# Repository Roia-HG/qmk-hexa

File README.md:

# qmk-hexa

 RP2040 칩을 사용한 멀티배열 스플릿 키보드

 3d 모델은 마그네틱 포고핀과 결합하는 구멍간격을 잘못 측정해서(데이터가 없었던 걸로 기억함) 개선이 필요함
그대로 사용하면 나처럼 한쪽을 약간 잘라서 사용해야하는 불상사가 일어남

 메인 오른쪽은 왼쪽 마그네틱 포고핀과 선을 연결하지 않음
양쪽 메인이 접속되면 row열 신호에 혼란이 발생하여 오류가 생길 것이기 때문에 스위치를 설치하는 것도 생각했지만
스위치를 설치할 적절한 방법이 떠오르지 않고 귀찮았으므로 연결하지 않고 사용하는 것으로 진행
즉, 메인 왼쪽은 네비키와 넘패드키 모두 좌우로 장착 가능하지만 메인 오른쪽은 오른쪽에만 장착 가능함.

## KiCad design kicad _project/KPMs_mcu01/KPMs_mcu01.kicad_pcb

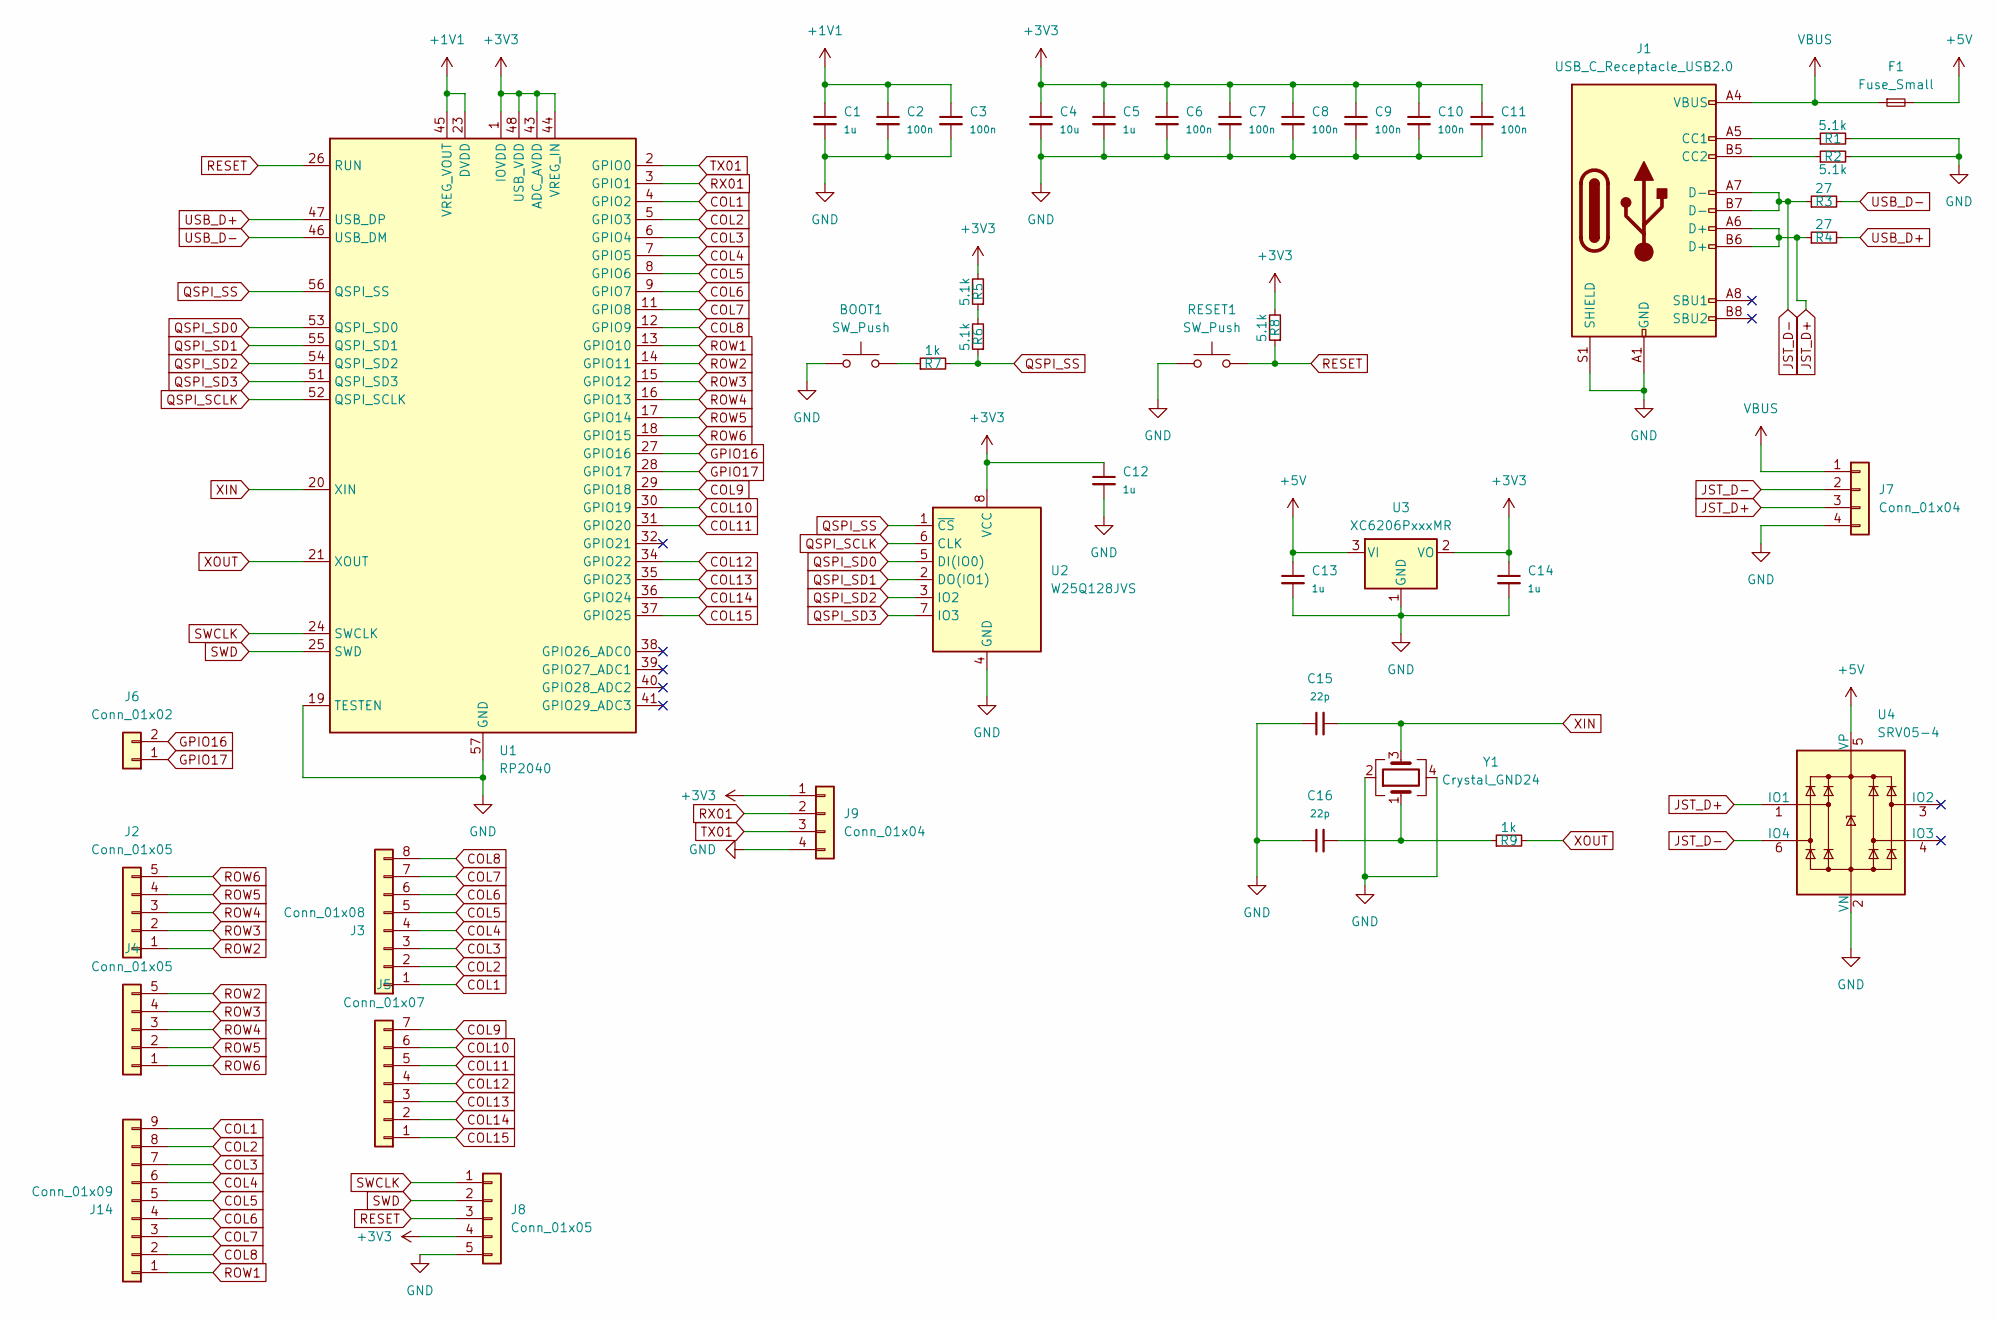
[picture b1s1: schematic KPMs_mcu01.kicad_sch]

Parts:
BOOT1: SW_Push; SW_SPST_TL3342
C1, C5, C12, C13, C14: 1u; C_0402_1005Metric
C2, C3, C6, C7, C8, C9, C10, C11: 100n; C_0402_1005Metric
C4: 10u; C_0402_1005Metric
C15, C16: 22p; C_0402_1005Metric
F1: Fuse_Small; MF-MSMF050-2
J1: USB_C_Receptacle_USB2.0; USB_C_Receptacle_HRO_TYPE-C-31-M-12
J2, J4: Conn_01x05; JST_SH_SM05B-SRSS-TB_1x05-1MP_P1.00mm_Horizontal
J3: Conn_01x08; JST_SH_SM08B-SRSS-TB_1x08-1MP_P1.00mm_Horizontal
J5: Conn_01x07; JST_SH_SM07B-SRSS-TB_1x07-1MP_P1.00mm_Horizontal
J6: Conn_01x02; PinHeader_1x02_P2.54mm_Vertical
J7, J9: Conn_01x04; JST_SH_SM04B-SRSS-TB_1x04-1MP_P1.00mm_Horizontal
J8: Conn_01x05; PinHeader_1x05_P2.00mm_Vertical
J14: Conn_01x09; JST_SH_SM09B-SRSS-TB_1x09-1MP_P1.00mm_Horizontal
R1, R2, R5, R6, R8: 5.1k; R_0402_1005Metric
R3, R4: 27; R_0402_1005Metric
R7, R9: 1k; R_0402_1005Metric
RESET1: SW_Push; SW_SPST_TL3342
U1: RP2040; QFN-56-1EP_7x7mm_P0.4mm_EP3.2x3.2mm
U2: W25Q128JVS; SOIC-8_5.23x5.23mm_P1.27mm
U3: XC6206PxxxMR; SOT-23-3
U4: SRV05-4; SOT-23-6-routable
Y1: Crystal_GND24; Crystal_SMD_3225-4Pin_3.2x2.5mm

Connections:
+1V1: C1.1, C2.1, C3.1, U1.23 (DVDD), U1.45 (VREG_VOUT), U1.50 (DVDD)
+3V3: C4.1, C5.1, C6.1, C7.1, C8.1, C9.1, C10.1, C11.1, C12.1, C14.1, J8.4, J9.1, R5.2, R8.2, U1.1 (IOVDD), U1.10 (IOVDD), U1.22 (IOVDD), U1.33 (IOVDD), U1.42 (IOVDD), U1.43 (ADC_AVDD), U1.44 (VREG_IN), U1.48 (USB_VDD), U1.49 (IOVDD), U2.8 (VCC), U3.2 (VO)
+5V: C13.1, F1.2, U3.3 (VI), U4.5 (VP)
COL1: J3.1, J14.9, U1.4 (GPIO2)
COL2: J3.2, J14.8, U1.5 (GPIO3)
COL3: J3.3, J14.7, U1.6 (GPIO4)
COL4: J3.4, J14.6, U1.7 (GPIO5)
COL5: J3.5, J14.5, U1.8 (GPIO6)
COL6: J3.6, J14.4, U1.9 (GPIO7)
COL7: J3.7, J14.3, U1.11 (GPIO8)
COL8: J3.8, J14.2, U1.12 (GPIO9)
COL9: J5.7, U1.29 (GPIO18)
COL10: J5.6, U1.30 (GPIO19)
COL11: J5.5, U1.31 (GPIO20)
COL12: J5.4, U1.34 (GPIO22)
COL13: J5.3, U1.35 (GPIO23)
COL14: J5.2, U1.36 (GPIO24)
COL15: J5.1, U1.37 (GPIO25)
GND: BOOT1.1, C1.2, C2.2, C3.2, C4.2, C5.2, C6.2, C7.2, C8.2, C9.2, C10.2, C11.2, C12.2, C13.2, C14.2, C15.1, C16.1, J1.A1 (GND), J1.A12 (GND), J1.B1 (GND), J1.B12 (GND), J1.S1 (SHIELD), J7.4, J8.5, J9.4, R1.2, R2.2, RESET1.1, U1.19 (TESTEN), U1.57 (GND), U2.4 (GND), U3.1 (GND), U4.2 (VN), Y1.2, Y1.4
GPIO16: J6.2, U1.27 (GPIO16)
GPIO17: J6.1, U1.28 (GPIO17)
JST_D+: J1.A6 (D+), J1.B6 (D+), J7.3, R4.1, U4.1 (IO1)
JST_D-: J1.A7 (D-), J1.B7 (D-), J7.2, R3.1, U4.6 (IO4)
unnamed: BOOT1.2, R7.1
unnamed: C16.2, R9.1, Y1.1
unnamed: J1.A5 (CC1), R1.1
unnamed: J1.B5 (CC2), R2.1
unnamed: R5.1, R6.2
QSPI_SCLK: U1.52 (QSPI_SCLK), U2.6 (CLK)
QSPI_SD0: U1.53 (QSPI_SD0), U2.5 (DI(IO0))
QSPI_SD1: U1.55 (QSPI_SD1), U2.2 (DO(IO1))
QSPI_SD2: U1.54 (QSPI_SD2), U2.3 (IO2)
QSPI_SD3: U1.51 (QSPI_SD3), U2.7 (IO3)
QSPI_SS: R6.1, R7.2, U1.56 (QSPI_SS), U2.1 (~CS)
RESET: J8.3, R8.1, RESET1.2, U1.26 (RUN)
ROW1: J14.1, U1.13 (GPIO10)
ROW2: J2.1, J4.5, U1.14 (GPIO11)
ROW3: J2.2, J4.4, U1.15 (GPIO12)
ROW4: J2.3, J4.3, U1.16 (GPIO13)
ROW5: J2.4, J4.2, U1.17 (GPIO14)
ROW6: J2.5, J4.1, U1.18 (GPIO15)
RX01: J9.2, U1.3 (GPIO1)
SWCLK: J8.1, U1.24 (SWCLK)
SWD: J8.2, U1.25 (SWD)
TX01: J9.3, U1.2 (GPIO0)
USB_D+: R4.2, U1.47 (USB_DP)
USB_D-: R3.2, U1.46 (USB_DM)
VBUS: F1.1, J1.A4 (VBUS), J1.A9 (VBUS), J1.B4 (VBUS), J1.B9 (VBUS), J7.1
XIN: C15.2, U1.20 (XIN), Y1.3
XOUT: R9.2, U1.21 (XOUT)

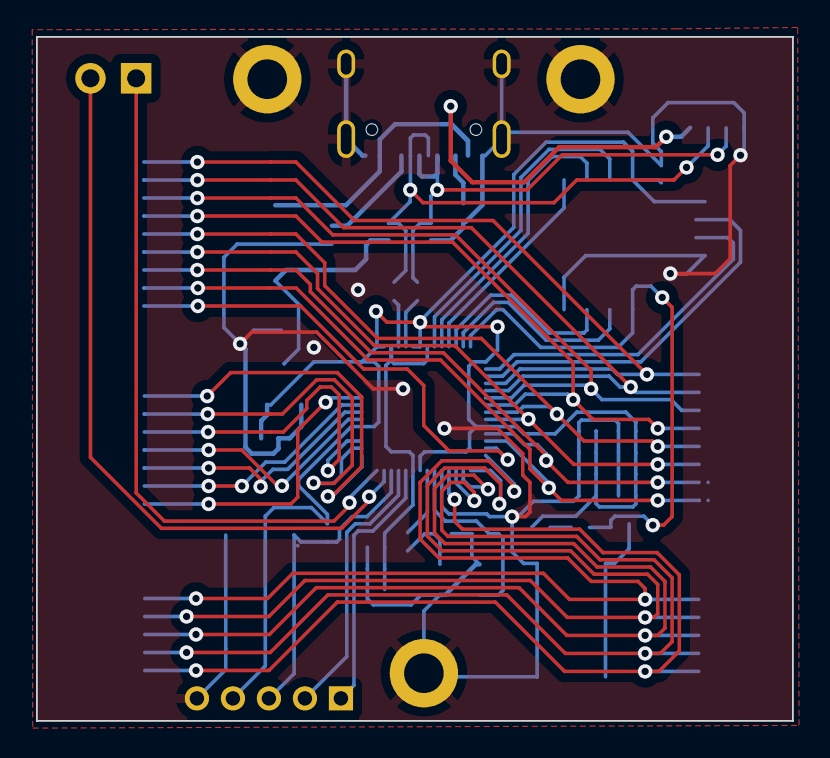
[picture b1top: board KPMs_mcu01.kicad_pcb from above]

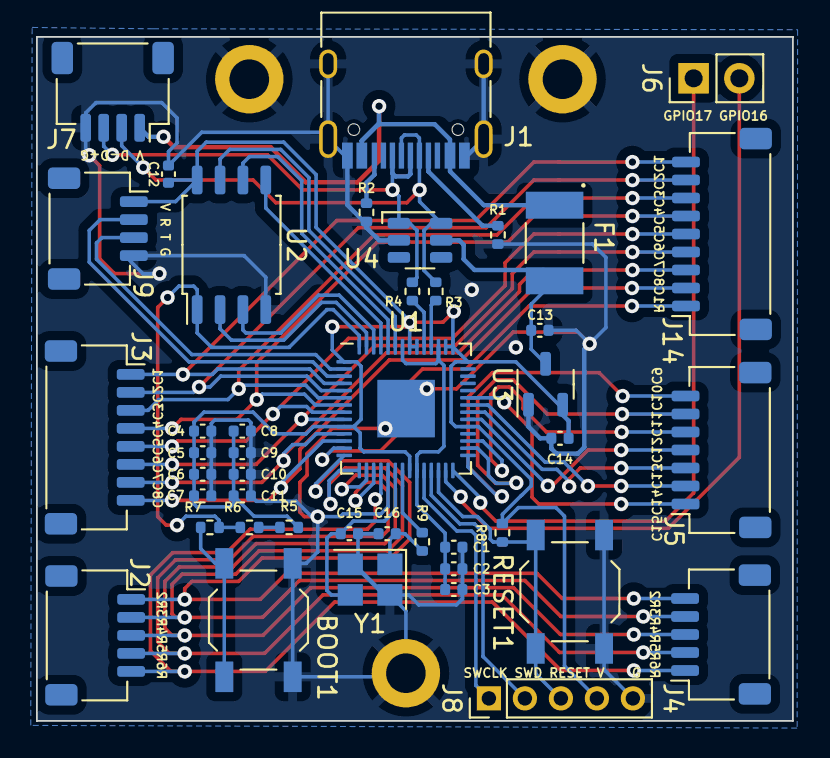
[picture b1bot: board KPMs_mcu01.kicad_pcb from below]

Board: 2 copper layers, 42.0 x 38.0 mm, 43 parts (43 on the bottom side), 50 nets.

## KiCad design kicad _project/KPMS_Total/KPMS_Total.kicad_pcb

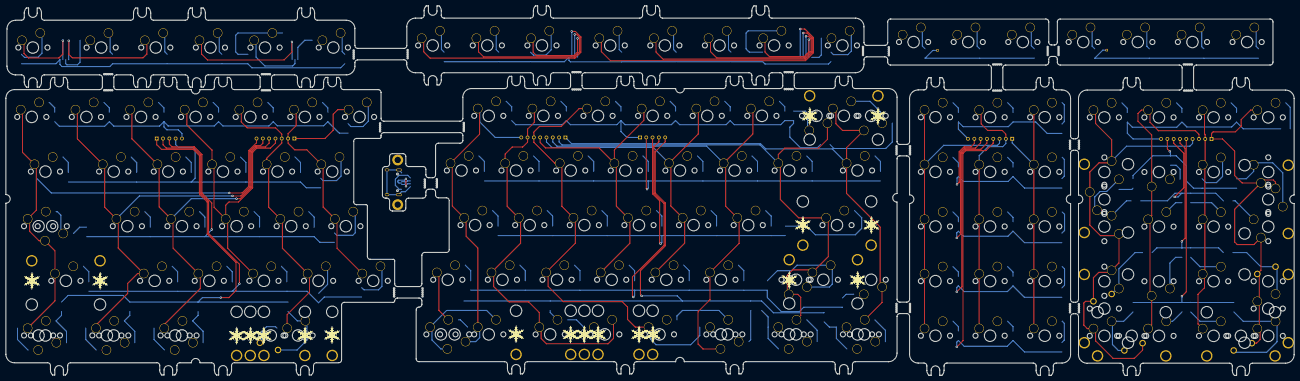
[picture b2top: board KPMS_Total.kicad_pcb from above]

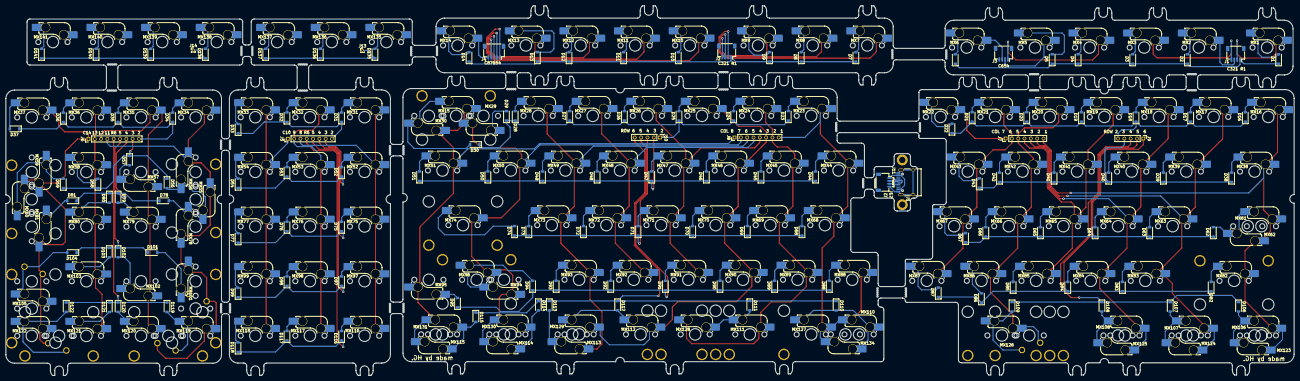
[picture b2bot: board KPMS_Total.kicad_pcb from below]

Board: 2 copper layers, 449.2 x 128.9 mm, 294 parts (290 on the bottom side), 186 nets.

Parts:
D1, D2, D3, D4, D5, D6, D7, D8, D9, D10, D11, D12, D13, D14, D16, D17, D18, D19, D20, D21, D22, D23, D24, D25, D26, D27, D28, D29, D30, D31, D32, D33, D34, D35, D36, D37, D38, D39, D40, D41, D42, D43, D44, D45, D46, D47, D48, D49, D50, D51, D52, D53, D54, D56, D57, D58, D59, D62, D63, D64, D65, D66, D67, D68, D69, D70, D71, D72, D73, D74, D75, D76, D77, D78, D79, D80, D81, D82, D83, D84, D85, D86, D87, D88, D89, D90, D91, D92, D93, D94, D95, D97, D98, D99, D101, D102, D103, D104, D106, D107, D108, D109, D110, D111, D112, D113, D114, D115, D116, D117, D118, D119, D120, D121, D122, D135, D136, D137, D138, D139, D140, D141: D_Small; D_SOD-123
J1, J2, J3: fn; JST_SH_SM04B-SRSS-TB_1x04-1MP_P1.00mm_Horizontal
J4: fn; JST_SH_SM05B-SRSS-TB_1x05-1MP_P1.00mm_Horizontal
J5, J8: Conn_01x08; PinHeader_1x08_P2.20mm_Vertical
J6: Conn_01x09; PinHeader_1x09_P2.20mm_Vertical
J7: Conn_01x07; PinHeader_1x07_P2.20mm_Vertical
J9, J10: Conn_01x05; PinHeader_1x05_P2.20mm_Vertical
J11: USB_C_Receptacle_USB2.0; USB_C_Receptacle_HRO_TYPE-C-31-M-12
J12: Conn_01x04; JST_SH_SM04B-SRSS-TB_1x04-1MP_P1.00mm_Horizontal
J13, J14: Conn_01x01; PinHeader_1x01_P1.00mm_Vertical
MX1, MX2, MX3, MX4, MX5, MX6, MX7, MX8, MX9, MX10, MX11, MX12, MX13, MX14, MX15, MX16, MX17, MX18, MX19, MX20, MX21, MX22, MX23, MX24, MX25, MX26, MX27, MX28, MX29, MX30, MX31, MX32, MX33, MX34, MX35, MX36, MX37, MX39, MX40, MX41, MX42, MX43, MX44, MX45, MX46, MX47, MX48, MX49, MX50, MX52, MX53, MX54, MX55, MX56, MX57, MX58, MX59, MX60, MX63, MX64, MX65, MX66, MX67, MX68, MX69, MX70, MX71, MX72, MX73, MX74, MX75, MX76, MX77, MX79, MX80, MX82, MX83, MX84, MX85, MX86, MX87, MX88, MX89, MX90, MX91, MX92, MX93, MX95, MX96, MX97, MX98, MX99, MX101, MX102, MX103, MX105, MX111, MX116, MX117, MX118, MX119, MX120, MX121, MX122, MX124, MX126, MX128, MX130, MX134, MX135, MX136, MX137, MX138, MX139, MX140, MX141: MX_SW_HS; SW_MX_HS_1u
MX38, MX51, MX123, MX125, MX127, MX129, MX131: MX_SW_HS; SW_MX_HS_1.5u
MX61: MX_SW_HS; SW_MX_HS_1.75u_STP_1.25
MX62, MX94: MX_SW_HS; SW_MX_HS_1.75u
MX78, MX81: MX_SW_HS; SW_MX_HS_1u_overlapkey
MX100, MX104, MX109, MX132, MX133: MX_SW_HS; SW_MX_1u
MX106, MX107, MX108, MX110, MX112, MX113, MX114, MX115: MX_SW_HS; SW_MX_HS_1.25u
S1, S9, S10, S11, S15, S16, S17: MX_stab; STAB_MX_P_2u
S2, S3, S5: MX_stab; STAB_MX_P_2.25u
S4, S6, S7, S8: MX_stab; STAB_MX_P_2.75u
S12: MX_stab; STAB_MX_P_7u_Left
S13: MX_stab; STAB_MX_P_6.25u_Right
S14: MX_stab; STAB_MX_P_7u_Right

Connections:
EXTRA_ROW1: D135.1 (K), D136.1 (K), D137.1 (K), J13.1
EXTRA_ROW2: D138.1 (K), D139.1 (K), D140.1 (K), D141.1 (K), J14.1
FnL_COL1: J1.2, MX1.1
FnL_COL2: J1.3, MX2.1
FnL_COL3: J1.4, MX3.1
FnL_COL4: J3.1, MX4.1
FnL_COL5: J3.2, MX5.1
FnL_COL6: J3.3, MX6.1
FnL_ROW1: D1.1 (K), D2.1 (K), D3.1 (K), D4.1 (K), D5.1 (K), D6.1 (K), J1.1
FnR_COL1: J2.2, MX7.1
FnR_COL2: J2.3, MX8.1
FnR_COL3: J2.4, MX9.1
FnR_COL4: J4.1, MX10.1
FnR_COL5: J4.2, MX11.1
FnR_COL6: J4.3, MX12.1
FnR_COL7: J4.4, MX13.1
FnR_COL8: J4.5, MX14.1
FnR_ROW1: D7.1 (K), D8.1 (K), D9.1 (K), D10.1 (K), D11.1 (K), D12.1 (K), D13.1 (K), D14.1 (K), J2.1
L_COL1: J7.7, MX16.1, MX38.1, MX61.1, MX62.2, MX82.1, MX106.1, MX123.2
L_COL2: J7.6, MX17.1, MX39.1, MX63.1, MX83.1, MX107.1, MX124.2
L_COL3: J7.5, MX18.1, MX40.1, MX64.1, MX84.1, MX108.1, MX125.2
L_COL4: J7.4, MX19.1, MX41.1, MX65.1, MX85.1
L_COL5: J7.3, MX20.1, MX42.1, MX66.1, MX86.1, MX109.1, MX126.1
L_COL6: J7.2, MX21.1, MX43.1, MX67.1, MX87.1
L_COL7: J7.1, MX22.1
L_ROW2: D16.1 (K), D17.1 (K), D18.1 (K), D19.1 (K), D20.1 (K), D21.1 (K), D22.1 (K), J9.5
L_ROW3: D38.1 (K), D39.1 (K), D40.1 (K), D41.1 (K), D42.1 (K), D43.1 (K), J9.4
L_ROW4: D62.1 (K), D63.1 (K), D64.1 (K), D65.1 (K), D66.1 (K), D67.1 (K), J9.3
L_ROW5: D82.1 (K), D83.1 (K), D84.1 (K), D85.1 (K), D86.1 (K), D87.1 (K), J9.2
L_ROW6: D106.1 (K), D107.1 (K), D108.1 (K), D109.1 (K), J9.1
NUM_COL11: J6.4, MX34.1, MX55.2, MX56.1, MX78.2, MX100.1, MX101.1, MX119.1, MX132.1
NUM_COL12: J6.3, MX35.1, MX57.2, MX79.1, MX102.2, MX120.1
NUM_COL13: J6.2, MX36.1, MX58.1, MX80.1, MX103.1, MX121.1
NUM_COL14: J6.1, MX37.1, MX59.1, MX60.1, MX81.1, MX104.1, MX105.1, MX122.1, MX133.1
NUM_ROW2: D34.1 (K), D35.1 (K), D36.1 (K), D37.1 (K), J6.9
NUM_ROW3: D56.1 (K), D57.1 (K), D58.1 (K), D59.1 (K), J6.8
NUM_ROW4: D78.1 (K), D79.1 (K), D80.1 (K), D81.1 (K), J6.7
NUM_ROW5: D101.1 (K), D102.1 (K), D103.1 (K), D104.1 (K), J6.6
NUM_ROW6: D119.1 (K), D120.1 (K), D121.1 (K), D122.1 (K), J6.5
unnamed: D1.2 (A), MX1.2
unnamed: D2.2 (A), MX2.2
unnamed: D3.2 (A), MX3.2
unnamed: D4.2 (A), MX4.2
unnamed: D5.2 (A), MX5.2
unnamed: D6.2 (A), MX6.2
unnamed: D7.2 (A), MX7.2
unnamed: D8.2 (A), MX8.2
unnamed: D9.2 (A), MX9.2
unnamed: D10.2 (A), MX10.2
unnamed: D11.2 (A), MX11.2
unnamed: D12.2 (A), MX12.2
unnamed: D13.2 (A), MX13.2
unnamed: D14.2 (A), MX14.2
unnamed: D16.2 (A), MX16.2
unnamed: D17.2 (A), MX17.2
unnamed: D18.2 (A), MX18.2
unnamed: D19.2 (A), MX19.2
unnamed: D20.2 (A), MX20.2
unnamed: D21.2 (A), MX21.2
unnamed: D22.2 (A), MX22.2
unnamed: D23.2 (A), MX23.2
unnamed: D24.2 (A), MX24.2
unnamed: D25.2 (A), MX25.2
unnamed: D26.2 (A), MX26.2
unnamed: D27.2 (A), MX27.2
unnamed: D28.2 (A), MX28.2
unnamed: D29.2 (A), MX29.2
unnamed: D30.2 (A), MX15.2, MX30.1
unnamed: D31.2 (A), MX31.2
unnamed: D32.2 (A), MX32.2
unnamed: D33.2 (A), MX33.2
unnamed: D34.2 (A), MX34.2
unnamed: D35.2 (A), MX35.2
unnamed: D36.2 (A), MX36.2
unnamed: D37.2 (A), MX37.2
unnamed: D38.2 (A), MX38.2
unnamed: D39.2 (A), MX39.2
unnamed: D40.2 (A), MX40.2
unnamed: D41.2 (A), MX41.2
unnamed: D42.2 (A), MX42.2
unnamed: D43.2 (A), MX43.2
unnamed: D44.2 (A), MX44.2
unnamed: D45.2 (A), MX45.2
unnamed: D46.2 (A), MX46.2
unnamed: D47.2 (A), MX47.2
unnamed: D48.2 (A), MX48.2
unnamed: D49.2 (A), MX49.2
unnamed: D50.2 (A), MX50.2
unnamed: D51.2 (A), MX51.2
unnamed: D52.2 (A), MX52.2
unnamed: D53.2 (A), MX53.2
unnamed: D54.2 (A), MX54.2
unnamed: D56.2 (A), MX55.1, MX56.2
unnamed: D57.2 (A), MX57.1
unnamed: D58.2 (A), MX58.2
unnamed: D59.2 (A), MX59.2, MX60.2
unnamed: D62.2 (A), MX61.2, MX62.1
unnamed: D63.2 (A), MX63.2
unnamed: D64.2 (A), MX64.2
unnamed: D65.2 (A), MX65.2
unnamed: D66.2 (A), MX66.2
unnamed: D67.2 (A), MX67.2
unnamed: D68.2 (A), MX68.2
unnamed: D69.2 (A), MX69.2
unnamed: D70.2 (A), MX70.2
unnamed: D71.2 (A), MX71.2
unnamed: D72.2 (A), MX72.2
unnamed: D73.2 (A), MX73.2
unnamed: D74.2 (A), MX74.2
unnamed: D75.2 (A), MX75.2
unnamed: D76.2 (A), MX76.2
unnamed: D77.2 (A), MX77.2
unnamed: D78.2 (A), MX78.1
unnamed: D79.2 (A), MX79.2
unnamed: D80.2 (A), MX80.2
unnamed: D81.2 (A), MX81.2
unnamed: D82.2 (A), MX82.2
unnamed: D83.2 (A), MX83.2
unnamed: D84.2 (A), MX84.2
unnamed: D85.2 (A), MX85.2
unnamed: D86.2 (A), MX86.2
unnamed: D87.2 (A), MX87.2
unnamed: D88.2 (A), MX88.2
unnamed: D89.2 (A), MX89.2
unnamed: D90.2 (A), MX90.2
unnamed: D91.2 (A), MX91.2
unnamed: D92.2 (A), MX92.2
unnamed: D93.2 (A), MX93.2
unnamed: D94.2 (A), MX94.1, MX96.2
unnamed: D95.2 (A), MX95.2
unnamed: D97.2 (A), MX97.2
unnamed: D98.2 (A), MX98.2
unnamed: D99.2 (A), MX99.2
unnamed: D101.2 (A), MX100.2, MX101.2
unnamed: D102.2 (A), MX102.1
unnamed: D103.2 (A), MX103.2
unnamed: D104.2 (A), MX104.2, MX105.2
unnamed: D106.2 (A), MX106.2, MX123.1
unnamed: D107.2 (A), MX107.2, MX124.1
unnamed: D108.2 (A), MX108.2, MX125.1
unnamed: D109.2 (A), MX109.2, MX126.2
unnamed: D110.2 (A), MX110.1, MX127.2, MX134.2
unnamed: D111.2 (A), MX111.2, MX128.1
unnamed: D112.2 (A), MX112.2, MX129.2
unnamed: D113.2 (A), MX113.1
unnamed: D114.2 (A), MX114.2, MX130.1
unnamed: D115.2 (A), MX115.2, MX131.1
unnamed: D116.2 (A), MX116.2
unnamed: D117.2 (A), MX117.2
unnamed: D118.2 (A), MX118.2
unnamed: D119.2 (A), MX119.2, MX132.2
unnamed: D120.2 (A), MX120.2
unnamed: D121.2 (A), MX121.2
unnamed: D122.2 (A), MX122.2, MX133.2
unnamed: D135.2 (A), MX135.2
unnamed: D136.2 (A), MX136.2
unnamed: D137.2 (A), MX137.2
unnamed: D138.2 (A), MX138.2
unnamed: D139.2 (A), MX139.2
unnamed: D140.2 (A), MX140.2
unnamed: D141.2 (A), MX141.2
unnamed: J11.A1 (GND), J11.A12 (GND), J11.B1 (GND), J11.B12 (GND), J11.S1 (SHIELD), J12.4
unnamed: J11.A4 (VBUS), J11.A9 (VBUS), J11.B4 (VBUS), J11.B9 (VBUS), J12.1
unnamed: J11.A7 (D-), J11.B7 (D-), J12.2
unnamed: J11.A6 (D+), J11.B6 (D+), J12.3
R_COL1: J8.8, MX23.1, MX44.1, MX68.1, MX88.1, MX110.2, MX127.1, MX134.1
R_COL2: J8.7, MX24.1, MX45.1, MX69.1, MX89.1, MX111.1, MX128.2
R_COL3: J8.6, MX25.1, MX46.1, MX70.1, MX90.1, MX112.1, MX129.1
R_COL4: J8.5, MX26.1, MX47.1, MX71.1, MX91.1
R_COL5: J8.4, MX27.1, MX48.1, MX72.1, MX92.1
R_COL6: J8.3, MX28.1, MX49.1, MX73.1, MX93.1, MX113.2
R_COL7: J8.2, MX29.1, MX50.1, MX74.1, MX94.2, MX96.1, MX114.1, MX130.2
R_COL8: J8.1, MX15.1, MX30.2, MX51.1, MX95.1, MX115.1, MX131.2
R_ROW2: D23.1 (K), D24.1 (K), D25.1 (K), D26.1 (K), D27.1 (K), D28.1 (K), D29.1 (K), D30.1 (K), J10.1
R_ROW3: D44.1 (K), D45.1 (K), D46.1 (K), D47.1 (K), D48.1 (K), D49.1 (K), D50.1 (K), D51.1 (K), J10.2
R_ROW4: D68.1 (K), D69.1 (K), D70.1 (K), D71.1 (K), D72.1 (K), D73.1 (K), D74.1 (K), J10.3
R_ROW5: D88.1 (K), D89.1 (K), D90.1 (K), D91.1 (K), D92.1 (K), D93.1 (K), D94.1 (K), D95.1 (K), J10.4
R_ROW6: D110.1 (K), D111.1 (K), D112.1 (K), D113.1 (K), D114.1 (K), D115.1 (K), J10.5
navi_COL8: J5.3, MX31.1, MX52.1, MX75.1, MX97.1, MX116.1
navi_COL9: J5.2, MX32.1, MX53.1, MX76.1, MX98.1, MX117.1
navi_COL10: J5.1, MX33.1, MX54.1, MX77.1, MX99.1, MX118.1
navi_ROW2: D31.1 (K), D32.1 (K), D33.1 (K), J5.8
navi_ROW3: D52.1 (K), D53.1 (K), D54.1 (K), J5.7
navi_ROW4: D75.1 (K), D76.1 (K), D77.1 (K), J5.6
navi_ROW5: D97.1 (K), D98.1 (K), D99.1 (K), J5.5
navi_ROW6: D116.1 (K), D117.1 (K), D118.1 (K), J5.4
